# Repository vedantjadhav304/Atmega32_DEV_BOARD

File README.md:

⚙️ AVR Development Board for ATmega32 TQFP Version

Welcome to the official repository for the AVR Development Board for ATmega32 (TQFP Version)! This project aims to develop a cost-effective, reliable, and accessible development board specifically designed for the ATmega32 TQFP microcontroller. It addresses the challenges engineers, students, and hobbyists face in sourcing affordable and high-quality development platforms, particularly within the Indian market.

## 🛠️ Project Overview

The scarcity of affordable, reliable AVR development boards has created hurdles for developers working on embedded systems projects. With this in mind, we— Vedant Jadhav and Abhishek Patil —have embarked on a mission to create an affordable solution designed to simplify development for the ATmega32 TQFP version.

### This development board aims to offer:
- 💡 Cost-effectiveness without compromising quality, keeping in mind the Indian market's pricing and availability constraints.
- ⚡ Reliability to ensure the board meets the demands of various embedded systems projects.
- 🧩 A compact and space-saving design** for those needing a smaller form factor in their applications.

## ✨ Key Features

- 💰 Affordable Innovation: The board is designed to minimize costs while still offering high-quality components and performance.
- 📦 Locally Sourced Components: To address supply chain issues in India, we’ve carefully selected components that are easily available in the local market.
- 🖇️ Compact Design: The TQFP package allows for a smaller and more space-efficient board without sacrificing functionality.
- 🔧 Development-Friendly: Whether you’re prototyping or working on full-scale projects, this board simplifies the process for both engineers and hobbyists.

## 📊 Technical Specifications

- Microcontroller: ATmega32 (TQFP Version)
- Form Factor: Compact, space-saving design
- Pins: Exposes all essential GPIO pins for flexible development
- Power Supply: Multiple input options for ease of use
- Programming Interface: Standard ISP header for programming and debugging

## 📂 Repository Contents

This repository contains the following key resources:

- 📝 Schematic Diagrams: Circuit diagrams detailing the board's layout and connections.
- 🖨️ PCB Design Files: All necessary files for manufacturing the PCB.
- 📋 Bill of Materials (BoM): A comprehensive list of components used in the development board, including sourcing information for the Indian market.
- 🔧 Firmware: Basic code examples and libraries to help users get started with the board, including sample projects to test various features of the ATmega32 microcontroller.

## 🚀 Future Plans

This is just the first iteration of our development board. We are working on enhancing the board’s capabilities and will release future versions with more features such as:
- 🌐 Advanced connectivity options
- 🧑‍🔧 Additional sensor interfaces
- 🔋 Enhanced power management systems

Stay tuned for updates as we continue to improve and expand the project to meet more sophisticated embedded system needs.

## 🤝 How to Contribute

We welcome contributions from the community! Whether you're fixing bugs, enhancing documentation, or suggesting new features, we encourage you to get involved. Please feel free to open an issue or submit a pull request.

1. 🪝 Fork the repository.
2. 🌱 Create a new branch (`git checkout -b feature-branch`).
3. 🛠️ Make your changes and commit them (`git commit -m 'Add new feature'`).
4. ⬆️ Push to the branch (`git push origin feature-branch`).
5. 🔄 Open a Pull Request.

## 📞 Contact

For any questions, suggestions, or collaboration inquiries, please feel free to reach out to us:

- Vedant Jadhav: [LinkedIn](https://www.linkedin.com/in/vedant-jadhav-912a8b260/)  
- Abishek Patil : [LinkedIn](https://www.linkedin.com/in/abhishek-patil-513774279/)

We’d love to hear from you!

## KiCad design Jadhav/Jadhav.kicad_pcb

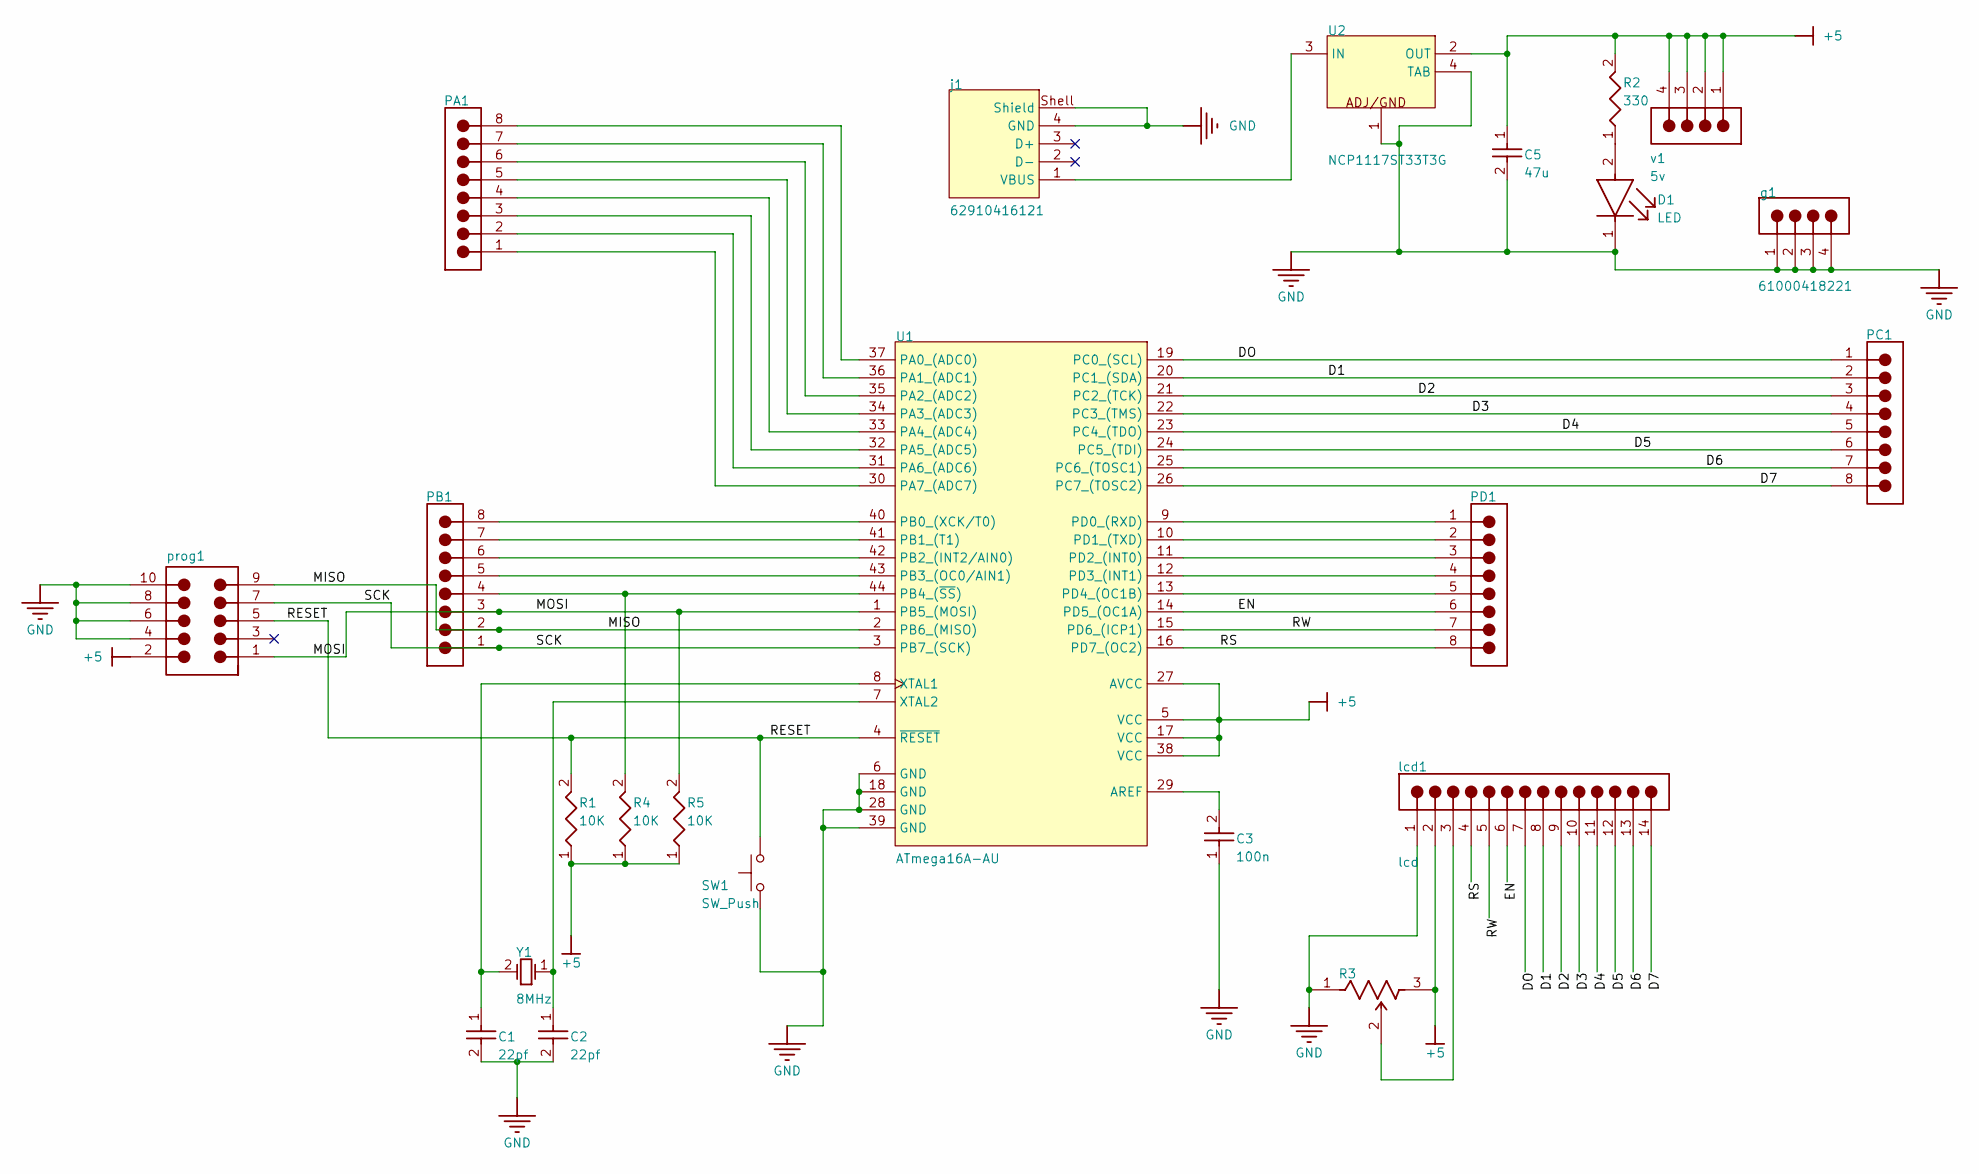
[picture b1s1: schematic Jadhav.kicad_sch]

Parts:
C1, C2, C3, C5: Capacitor 100nF +/-20% 25V 0402; CAP_9-J_8-E-X_AVX; TOLERANCE 10%; VOLTAGE RATING 25V
D1: LED; LED_D3.0mm; REVERSE VOLTAGE 5V; VOLTAGE 2V
PA1: CONN8_61300811121_WRE; VOLTAGE RATING 250V; CURRENT RATING 3A
PB1: CONN8_61300811121_WRE; VOLTAGE RATING 250V; CURRENT RATING 3A
PC1: CONN8_61300811121_WRE; VOLTAGE RATING 250V; CURRENT RATING 3A
PD1: CONN8_61300811121_WRE; VOLTAGE RATING 250V; CURRENT RATING 3A
R1, R2, R4, R5: Resistor 470R +/-5% 0805 125 mW; R_Axial_DIN0207_L6.3mm_D2.5mm_P7.62mm_Horizontal; TOLERANCE 5%
R3: RES3_PV36W103C01B00_BRN; POWER RATING 500mW; RESISTANCE TOLERANCE 10%
SW1: SW_Push; SW_PUSH_1P1T_6x3.5mm_H5.0_APEM_MJTP1250
U1: ATmega16A-AU; TQFP-44_10x10mm_P0.8mm
U2: NCP1117ST33T3G; SOT223-3_ONS; VOLTAGE RATING 75 V; TOLERANCE 1%
Y1: 8MHz; ATS08A-E_CTS; VOLTAGE RATING 250 V; TOLERANCE 1%
g1: 61000418221; SAMTEC_TS-104-T-AA; VOLTAGE RATING 250V; CURRENT RATING 3A
j1: 62910416121; CURRENT RATING 1.5A
lcd1: lcd; 14_CONN_SBH11-PBPC-D07-ST-BK_SUL; CURRENT RATING 3A
prog1: CONN_SBH11-PBPC-D05-ST-BK_SUL; FLAMMABILITY RATING UL94 V-0; CURRENT RATING 3A
v1: 5v; SAMTEC_TS-104-T-AA; VOLTAGE RATING 250V; CURRENT RATING 3A

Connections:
+5: C5.1, R1.1, R2.2, R3.3 (CW), R4.1, R5.1, U1.5 (VCC), U1.17 (VCC), U1.27 (AVCC), U1.38 (VCC), U2.2 (OUT), lcd1.2, prog1.2, v1.1, v1.2, v1.3, v1.4
/D1: PC1.2, U1.20 (PC1_(SDA)), lcd1.8
/D2: PC1.3, U1.21 (PC2_(TCK)), lcd1.9
/D3: PC1.4, U1.22 (PC3_(TMS)), lcd1.10
/D4: PC1.5, U1.23 (PC4_(TDO)), lcd1.11
/D5: PC1.6, U1.24 (PC5_(TDI)), lcd1.12
/D6: PC1.7, U1.25 (PC6_(TOSC1)), lcd1.13
/D7: PC1.8, U1.26 (PC7_(TOSC2)), lcd1.14
/DO: PC1.1, U1.19 (PC0_(SCL)), lcd1.7
/EN: PD1.6, U1.14 (PD5_(OC1A)), lcd1.6
/MISO: PB1.2, U1.2 (PB6_(MISO)), prog1.9
/MOSI: PB1.3, R5.2, U1.1 (PB5_(MOSI)), prog1.1
/RESET: R1.2, SW1.2, U1.4 (~RESET), prog1.5
/RS: PD1.8, U1.16 (PD7_(OC2)), lcd1.4
/RW: PD1.7, U1.15 (PD6_(ICP1)), lcd1.5
/SCK: PB1.1, U1.3 (PB7_(SCK)), prog1.7
GND: C1.2, C2.2, C3.1, C5.2, D1.1 (C), R3.1 (CCW), SW1.1, U1.6 (GND), U1.18 (GND), U1.28 (GND), U1.39 (GND), U2.1 (ADJ/GND), U2.4 (TAB), g1.1, g1.2, g1.3, g1.4, j1.4 (GND), j1.Shell (Shield), lcd1.1, prog1.4, prog1.6, prog1.8, prog1.10
unnamed: D1.2 (A), R2.1
unnamed: R3.2 (WIPER), lcd1.3
unnamed: C3.2, U1.29 (AREF)
unnamed: PA1.8, U1.37 (PA0_(ADC0))
unnamed: PA1.7, U1.36 (PA1_(ADC1))
unnamed: PA1.6, U1.35 (PA2_(ADC2))
unnamed: PA1.5, U1.34 (PA3_(ADC3))
unnamed: PA1.4, U1.33 (PA4_(ADC4))
unnamed: PA1.3, U1.32 (PA5_(ADC5))
unnamed: PA1.2, U1.31 (PA6_(ADC6))
unnamed: PA1.1, U1.30 (PA7_(ADC7))
unnamed: PB1.8, U1.40 (PB0_(XCK/T0))
unnamed: PB1.7, U1.41 (PB1_(T1))
unnamed: PB1.6, U1.42 (PB2_(INT2/AIN0))
unnamed: PB1.5, U1.43 (PB3_(OC0/AIN1))
unnamed: PB1.4, R4.2, U1.44 (PB4_(~SS))
unnamed: PD1.1, U1.9 (PD0_(RXD))
unnamed: PD1.2, U1.10 (PD1_(TXD))
unnamed: PD1.3, U1.11 (PD2_(INT0))
unnamed: PD1.4, U1.12 (PD3_(INT1))
unnamed: PD1.5, U1.13 (PD4_(OC1B))
unnamed: C1.1, U1.8 (XTAL1), Y1.2
unnamed: C2.1, U1.7 (XTAL2), Y1.1
unnamed: U2.3 (IN), j1.1 (VBUS)

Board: 2 copper layers, 23 parts (0 on the bottom side), 41 nets, no tracks yet.

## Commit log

2024-07-26 Initial commit for Atemega Dev Board , Footprint assignment done , PCB layout pending
2024-07-26 Initial PCB layout commit
2024-07-26 Updated footprint for LCD
2024-07-28 Initial routing
2024-07-28 Routing, Zone filling , todo : fix v1g1 errors
2024-07-28 Grounding done , todo v1g1
2024-08-01 g1 v1 fixed
2024-08-01 Changes made to library name
2024-08-01 Gerber Files
2024-10-10 README.md
